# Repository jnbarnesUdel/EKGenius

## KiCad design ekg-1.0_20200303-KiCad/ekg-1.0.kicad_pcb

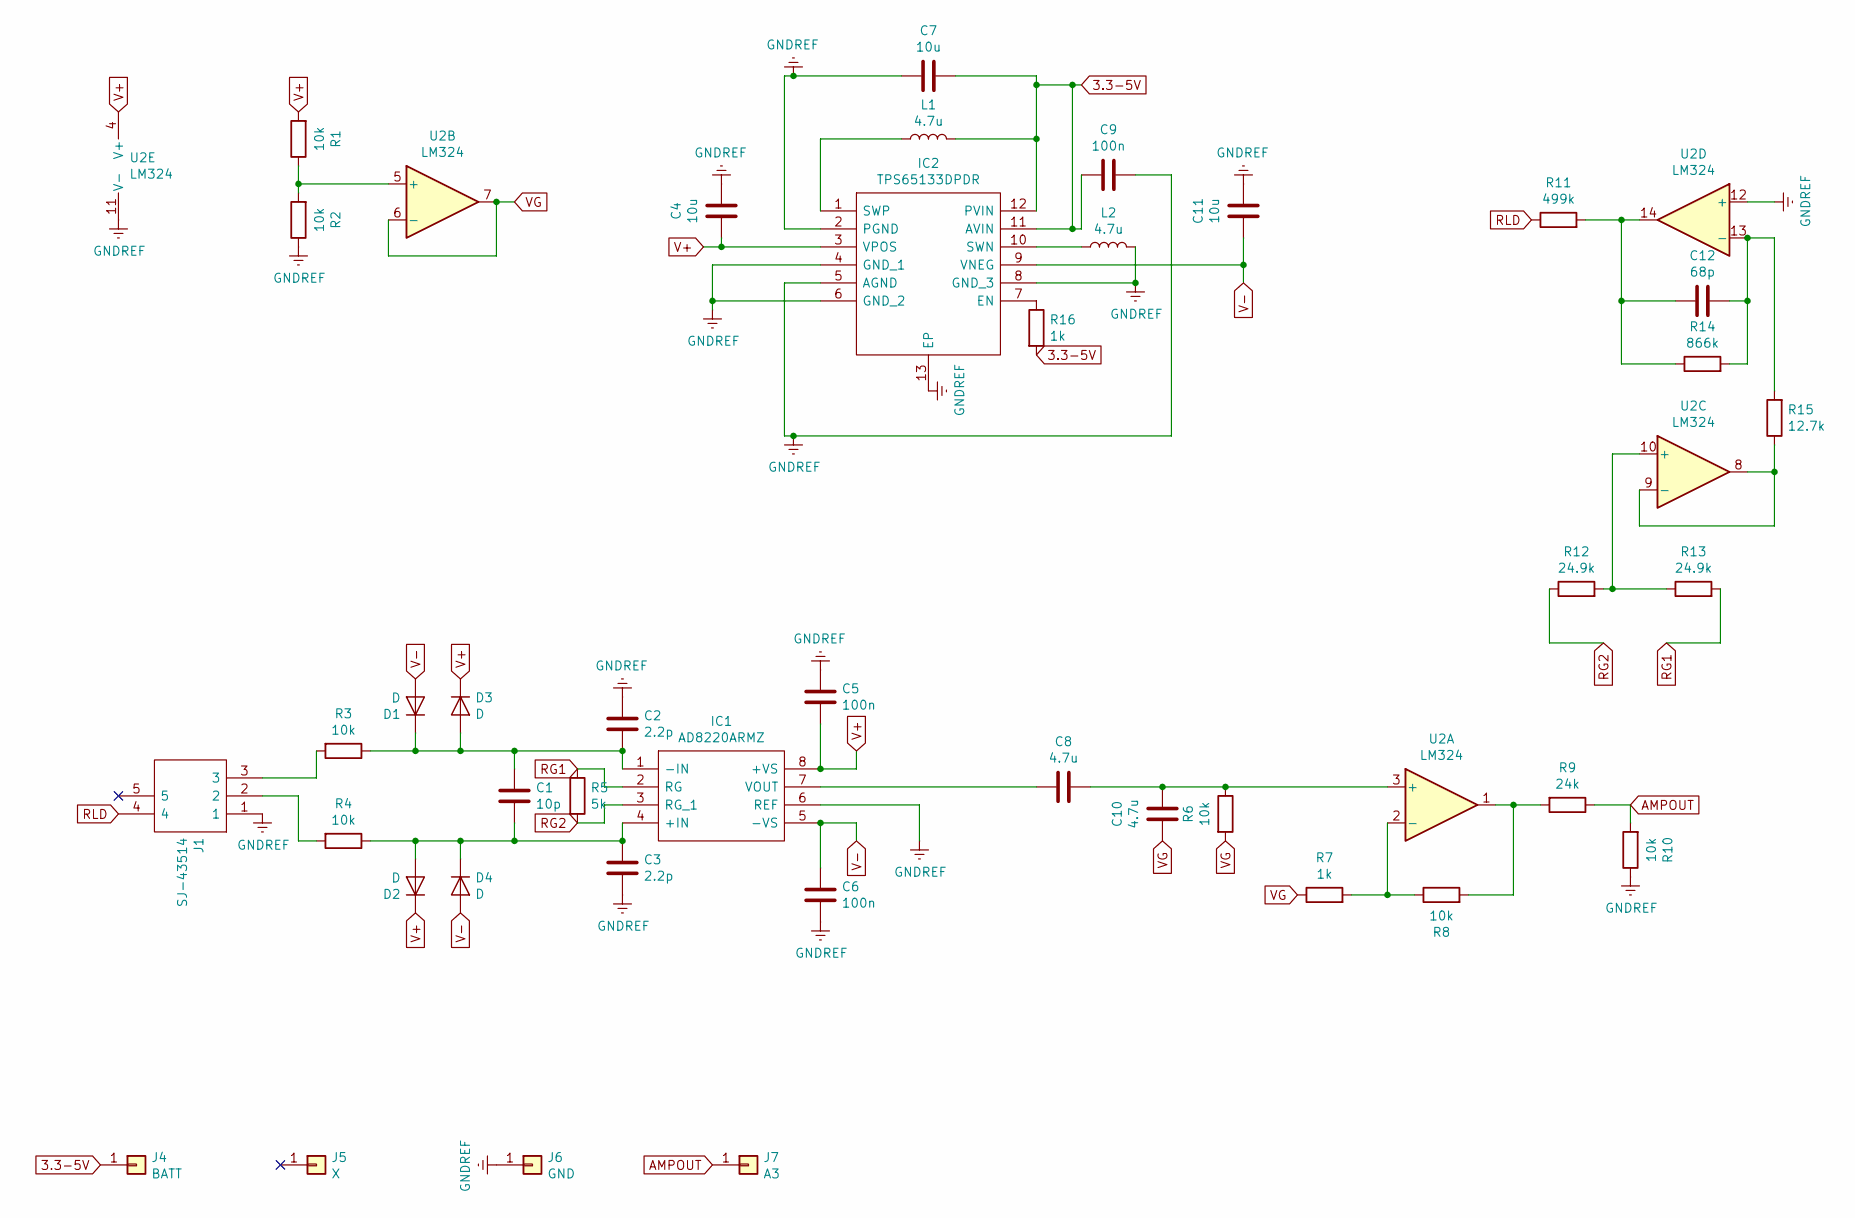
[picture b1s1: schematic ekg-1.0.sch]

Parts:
C1: 10p; C_0805_2012Metric
C2, C3: 2.2p; C_0805_2012Metric
C4, C7, C11: 10u; C_0805_2012Metric
C5, C6, C9: 100n; C_0805_2012Metric
C8, C10: 4.7u; C_0805_2012Metric
C12: 68p; C_0805_2012Metric
D1, D2, D3, D4: D; D_SOD-323F
IC1: AD8220ARMZ; SOP65P490X110-8N; Manufacturer_Part_Number AD8220ARMZ; Mouser Part Number 584-AD8220ARMZ
IC2: TPS65133DPDR; SON45P300X300X80-13N-D; Manufacturer_Part_Number TPS65133DPDR; Mouser Part Number 595-TPS65133DPDR
J1: SJ-43514; SJ43514; Manufacturer_Part_Number SJ-43514; Mouser Part Number 490-SJ-43514
J4: BATT; PinHeader_1x01_P2.54mm_Vertical
J5: X; PinHeader_1x01_P2.54mm_Vertical
J6: GND; PinHeader_1x01_P2.54mm_Vertical
J7: A3; PinHeader_1x01_P2.54mm_Vertical
L1, L2: 4.7u; L_1008_2520Metric
R1, R2, R3, R4, R6, R8, R10: 10k; R_0805_2012Metric
R5: 5k; R_0805_2012Metric
R7, R16: 1k; R_0805_2012Metric
R9: 24k; R_0805_2012Metric
R11: 499k; R_0805_2012Metric
R12, R13: 24.9k; R_0805_2012Metric
R14: 866k; R_0805_2012Metric
R15: 12.7k; R_0805_2012Metric
U2: LM324; SOIC-14_3.9x8.7mm_P1.27mm

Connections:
3.3-5V: C7.2, C9.1, IC2.11 (AVIN), IC2.12 (PVIN), J4.1, L1.2, R16.2
AMPOUT: J7.1, R9.1, R10.2
GNDREF: C2.1, C3.2, C4.2, C5.1, C6.2, C7.1, C9.2, C11.2, IC1.6 (REF), IC2.2 (PGND), IC2.4 (GND_1), IC2.5 (AGND), IC2.6 (GND_2), IC2.8 (GND_3), IC2.13 (EP), J1.1, J6.1, L2.2, R2.1, R10.1, U2.11 (V-), U2.12 (+)
unnamed: C1.1, C2.2, D1.1 (K), D3.2 (A), IC1.1 (-IN), R3.1
unnamed: C1.2, C3.1, D2.2 (A), D4.1 (K), IC1.4 (+IN), R4.1
unnamed: C8.1, IC1.7 (VOUT)
unnamed: C8.2, C10.2, R6.1, U2.3 (+)
unnamed: C12.1, R14.2, R15.2, U2.13 (-)
unnamed: C12.2, R11.2, R14.1, U2.14
unnamed: IC2.1 (SWP), L1.1
unnamed: IC2.7 (EN), R16.1
unnamed: IC2.10 (SWN), L2.1
unnamed: J1.2, R4.2
unnamed: J1.3, R3.2
unnamed: R1.1, R2.2, U2.5 (+)
unnamed: R7.2, R8.1, U2.2 (-)
unnamed: R8.2, R9.2, U2.1
unnamed: R12.2, R13.1, U2.10 (+)
unnamed: R15.1, U2.8, U2.9 (-)
RG1: IC1.2 (RG), R5.1, R13.2
RG2: IC1.3 (RG_1), R5.2, R12.1
RLD: J1.4, R11.1
V+: C4.1, C5.2, D2.1 (K), D3.1 (K), IC1.8 (+VS), IC2.3 (VPOS), R1.2, U2.4 (V+)
V-: C6.1, C11.1, D1.2 (A), D4.2 (A), IC1.5 (-VS), IC2.9 (VNEG)
VG: C10.1, R6.2, R7.1, U2.6 (-), U2.7

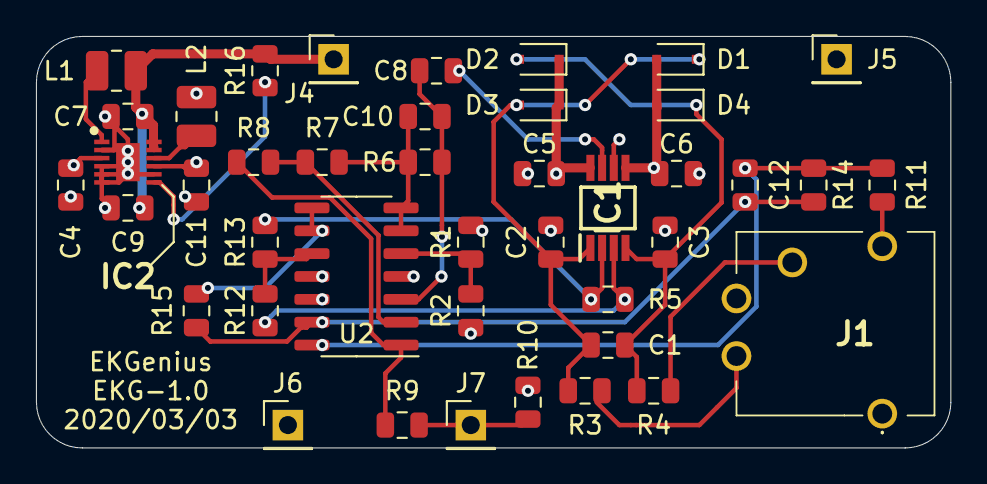
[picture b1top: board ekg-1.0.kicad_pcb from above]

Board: 4 copper layers, 50.8 x 22.9 mm, 42 parts (0 on the bottom side), 25 nets.

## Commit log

2019-09-23 message
2019-09-25 Rename TextTwist.html to index.html
    Changed name to index so that heroku can see it
2019-09-25 Add files via upload
    added database so heroku can see
2019-09-25 think i need for heroku
2019-09-25 changed url away from paiza server
2019-09-25 For heroku
2019-10-22 Rename letters.php to index.php
2019-10-22 Rename index.php to serverside.php
2019-11-05 added test sql database
2019-11-05 Update serverside.php
    changed to look in test sql database
2019-11-07 Update index.html
    add button for enter new patient
2019-11-07 Add files via upload
    new patient page
2019-11-07 Update TT.js
    Added enter data for new patient function
2019-11-07 added new path for inserting into database
2019-11-07 debugging
2019-12-03 adding dygraphs for graphing stuff
2019-12-03 dygraph css for graphing
2019-12-03 test data
2019-12-03 test if csv shows
2019-12-03 re add data after changing format
2019-12-03 new filtered data
2019-12-03 added pretty data
2020-05-19 test push
2020-05-19 removed test file
2020-05-19 Hardware Files
    Added KiCad design files, micro-controller code, and recorded data.
2020-05-20 Create New EKGenus webpage stuff
2020-05-20 new webpage stuff
    new webpage stuff
2020-05-20 phone app
